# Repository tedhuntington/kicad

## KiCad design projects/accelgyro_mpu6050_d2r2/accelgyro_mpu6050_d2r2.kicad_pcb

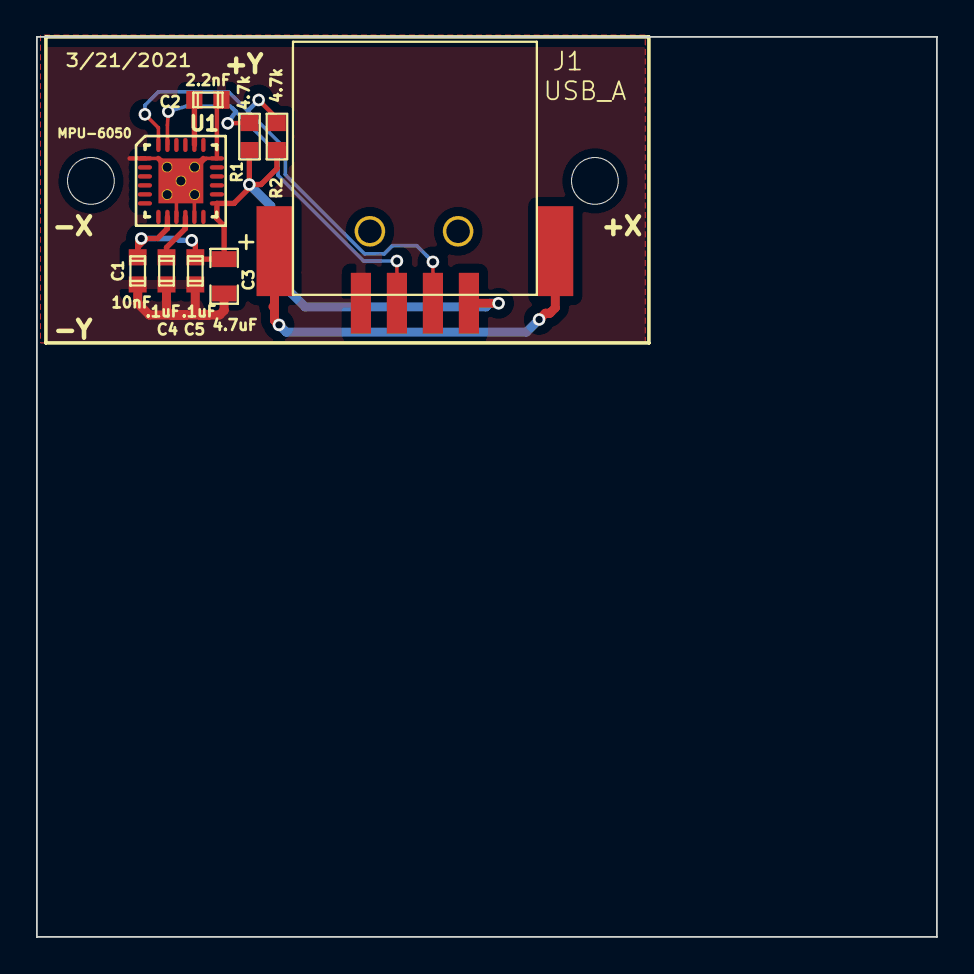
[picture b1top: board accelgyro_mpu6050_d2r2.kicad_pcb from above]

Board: 2 copper layers, 50.0 x 50.0 mm, 11 parts (0 on the bottom side), 6 nets.

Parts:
C1: 10nF; TED_SM0603_C
C2: 2.2nF; TED_SM0603_C
C3: 4.7uF; TED_SM2012_0805_ELEC_C
C4, C5: .1uF; TED_SM0603_C
H1, H2: HOLE; TED_Hole_2_6mm
J1: USB_A; TED_USB_A_SMD
R1, R2: 4.7k; TED_SM0603_R
U1: MPU-6050; TED_QFN24+1_NO_PASTE

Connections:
GND: C1.2, C2.2, C3.2, C4.2, C5.2, J1.4, U1.1, U1.9, U1.11, U1.18, U1.25
unnamed: C2.1, U1.20
unnamed: C4.1, U1.10
SCL: J1.3, R1.2, U1.23
SDA: J1.2, R2.2, U1.24
Vdd: C1.1, C3.1, C5.1, J1.1, R1.1, R2.1, U1.8, U1.13

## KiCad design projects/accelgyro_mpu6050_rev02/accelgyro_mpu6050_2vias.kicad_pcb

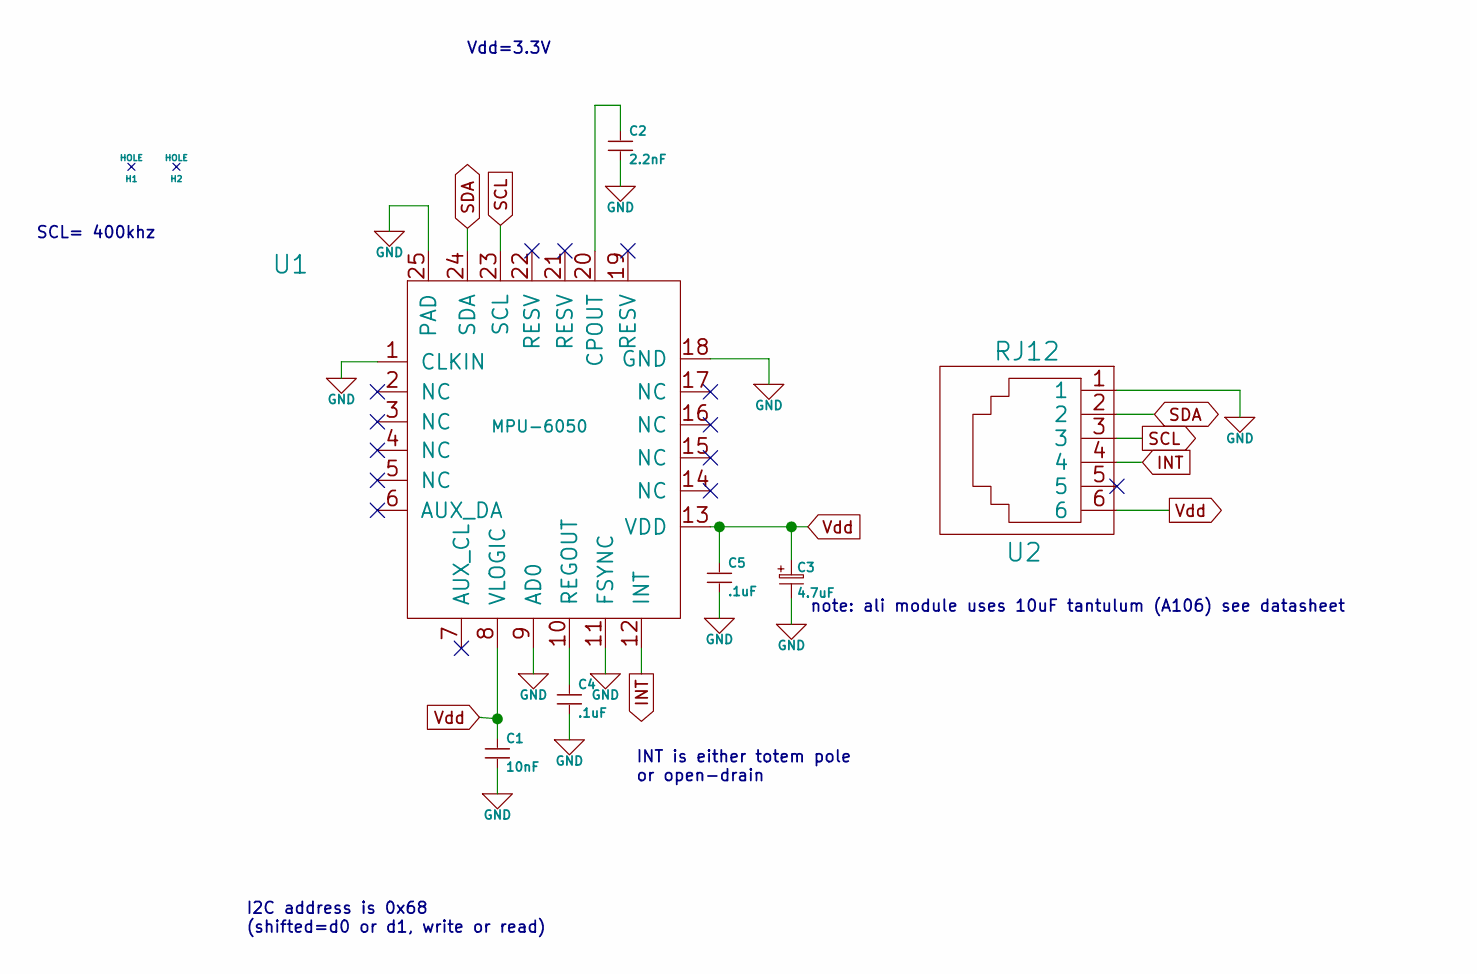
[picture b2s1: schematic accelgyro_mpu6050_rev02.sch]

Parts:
C1: 10nF; TED_SM0603_C
C2: 2.2nF; TED_SM0603_C
C3: 4.7uF; TED_SM2012_0805_ELEC_C
C4, C5: .1uF; TED_SM0603_C
H1, H2: HOLE; TED_Hole_2_6mm
U1: MPU-6050; TED_QFN24+1_NO_PASTE
U2: RJ12; TED_RJ12_Through_Hole

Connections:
GND: C1.2, C2.2, C3.2, C4.2, C5.2, U1.1 (CLKIN), U1.9 (AD0), U1.11 (FSYNC), U1.18 (GND), U1.25 (PAD), U2.1
INT: U1.12 (INT), U2.4
unnamed: C2.1, U1.20 (CPOUT)
unnamed: C4.1, U1.10 (REGOUT)
SCL: U1.23 (SCL), U2.3
SDA: U1.24 (SDA), U2.2
Vdd: C1.1, C3.1, C5.1, U1.8 (VLOGIC), U1.13 (VDD), U2.6

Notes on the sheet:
Vdd=3.3V
I2C address is 0x68 (shifted=d0 or d1, write or read)
INT is either totem pole or open-drain
SCL= 400khz
note: ali module uses 10uF tantulum (A106) see datasheet

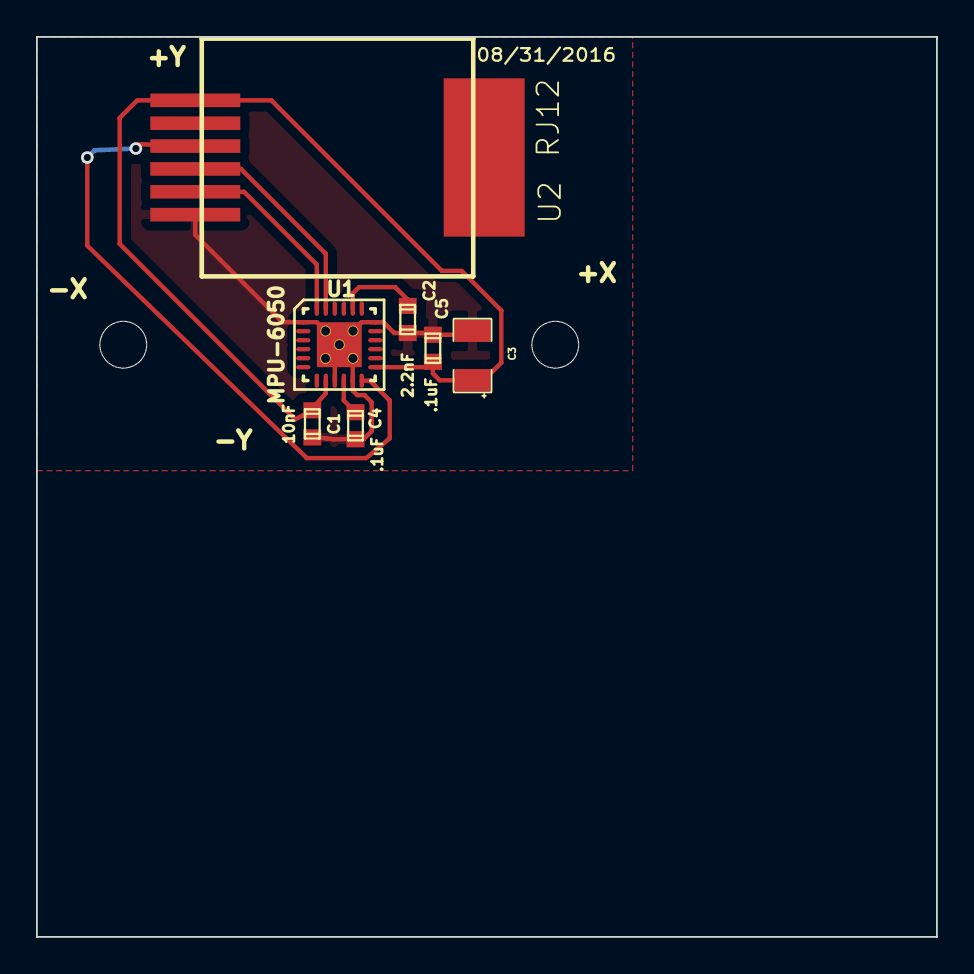
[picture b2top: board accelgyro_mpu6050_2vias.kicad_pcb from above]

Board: 2 copper layers, 50.0 x 50.0 mm, 9 parts (0 on the bottom side), 7 nets.

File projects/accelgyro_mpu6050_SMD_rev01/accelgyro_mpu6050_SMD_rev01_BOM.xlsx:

accelgyro_mpu6050_SMD_rev01
Sun 23 Jul 2017 10:05:59 AM PDT
Eeschema 4.0.6-e0-6349~53~ubuntu16.04.1
Component Count:9
Ref | Qnty | Value | Part | Part# | Unit Cost | Total Cost | Major Distributor | Minor Distributor
C1, | 1 | 10nF | capacitors:SM0603_C | VJ0603Y103MXAAC | 0.1 | 0.1 | Mouser
C2, | 1 | 2.2nF | capacitors:SM0603_C | GRM188R71H222KA01D | 0.1 | 0.1 | Digi-Key/Mouser
C3, | 1 | 4.7uF | capacitors:SM3216_1206_ELEC_C | TAJA475K025RNJ | 0.1 | 0.1 | Mouser
C4, C5, | 2 | .1uF | capacitors:SM0603_C | Vj0603V104ZXAPW1BC | 0.1 | 0.2 | Mouser
H1, H2, | 2 | HOLE | holes:Hole_2_6mm |  | 0 | 0
U1, | 1 | MPU-6050 | ICs:QFN24+1_NO_PASTE |  | 0.97 | 0.97 |  | AliExpress
U2, | 1 | RJ12 | connectors:RJ12_855135002 | 855135002 | 0.98 | 0.98 | Mouser
 |  |  |  |  |  | 2.45

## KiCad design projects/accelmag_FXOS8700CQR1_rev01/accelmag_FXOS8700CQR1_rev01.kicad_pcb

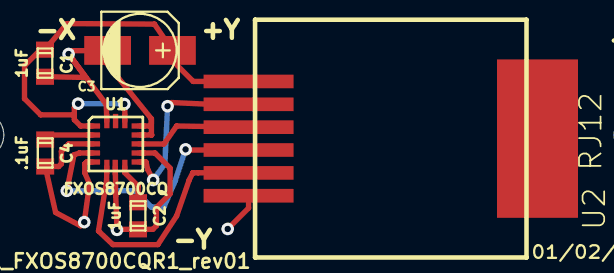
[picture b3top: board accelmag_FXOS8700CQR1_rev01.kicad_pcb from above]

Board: 2 copper layers, 8 parts (0 on the bottom side), 8 nets.

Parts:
C1, C2: 1uF; TED_SM0603_C
C3: 4.7uF; TED_c_elec_4.3x4.3
C4: .1uF; TED_SM0603_C
H1, H2: HOLE; TED_Hole_2_6mm
U1: FXOS8700CQ; TED_QFN16_3x5
U2: RJ12; TED_RJ12_855135002

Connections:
GND: C1.2, C2.2, C3.2, C4.2, U1.3, U1.5, U1.7, U1.10, U1.12, U1.13, U1.16, U2.1
INT1: U1.11, U2.4
INT2: U1.9, U2.5
unnamed: C2.1, U1.8
unnamed: C4.1, U1.2
SCL: U1.4, U2.3
SDA: U1.6, U2.2
Vdd: C1.1, C3.1, U1.1, U1.14, U2.6
